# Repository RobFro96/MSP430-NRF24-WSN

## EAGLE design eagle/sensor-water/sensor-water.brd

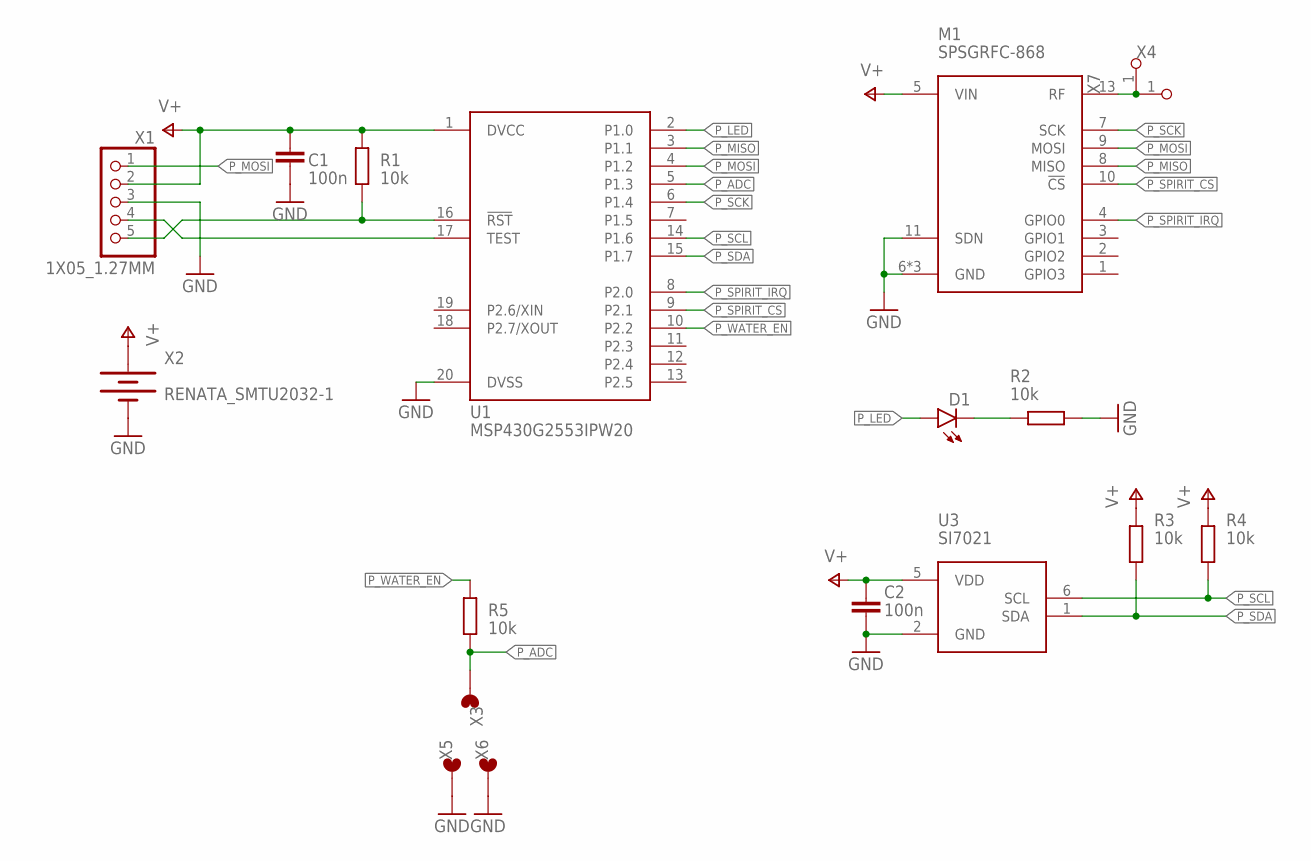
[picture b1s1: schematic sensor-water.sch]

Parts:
C1, C2: 100n; C0805_HAND
D1: LEDCHIPLED_0805; CHIPLED_0805
M1: SPSGRFC-868
R1, R2, R3, R4, R5: 10k; R0805_HAND
U1: MSP430G2553IPW20; PW20
U3: SI7021; DFN6-3X3
X1: 1X05_1.27MM
X2: RENATA_SMTU2032-1
X3, X5, X6: WASSERW_FOOTS
X4, X7: PINHD_1_RND; 1X01_NOSILK

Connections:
GND: C1.2, C2.2, M1.6 (GND), M1.11 (SDN), M1.12 (GND), M1.14 (GND), R2.2, U1.20 (DVSS), U3.2 (GND), X1.3, X2.2 (-), X5.1, X6.1
unnamed: D1.C, R2.1
unnamed: R1.1, U1.16 (!RST!), X1.5
unnamed: U1.17 (TEST), X1.4
unnamed: M1.13 (RF), X4.1, X7.1
P_ADC: R5.1, U1.5 (P1.3), X3.1
P_LED: D1.A, U1.2 (P1.0)
P_MISO: M1.8 (MISO), U1.3 (P1.1)
P_MOSI: M1.9 (MOSI), U1.4 (P1.2), X1.1
P_SCK: M1.7 (SCK), U1.6 (P1.4)
P_SCL: R4.1, U1.14 (P1.6), U3.6 (SCL)
P_SDA: R3.1, U1.15 (P1.7), U3.1 (SDA)
P_SPIRIT_!CS: M1.10 (!CS), U1.9 (P2.1)
P_SPIRIT_IRQ: M1.4 (GPIO0), U1.8 (P2.0)
P_WATER_EN: R5.2, U1.10 (P2.2)
V+: C1.1, C2.1, M1.5 (VIN), R1.2, R3.2, R4.2, U1.1 (DVCC), U3.5 (VDD), X1.2, X2.1 (+)

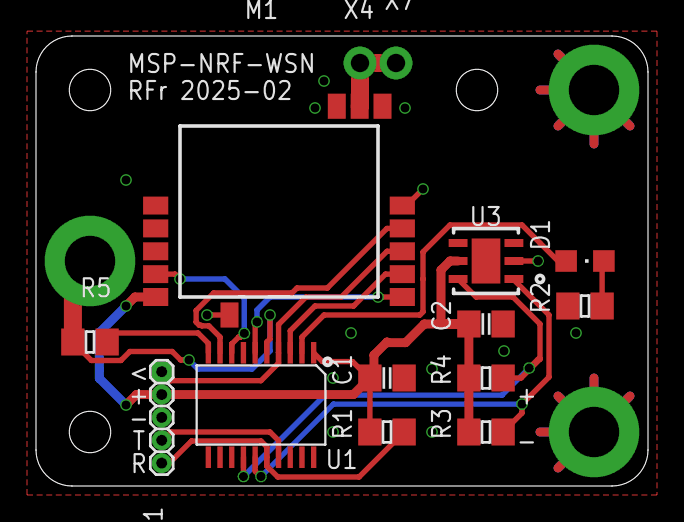
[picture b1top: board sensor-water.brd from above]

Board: 2 copper layers, 34.0 x 25.0 mm, 18 parts (1 on the bottom side), 16 nets.

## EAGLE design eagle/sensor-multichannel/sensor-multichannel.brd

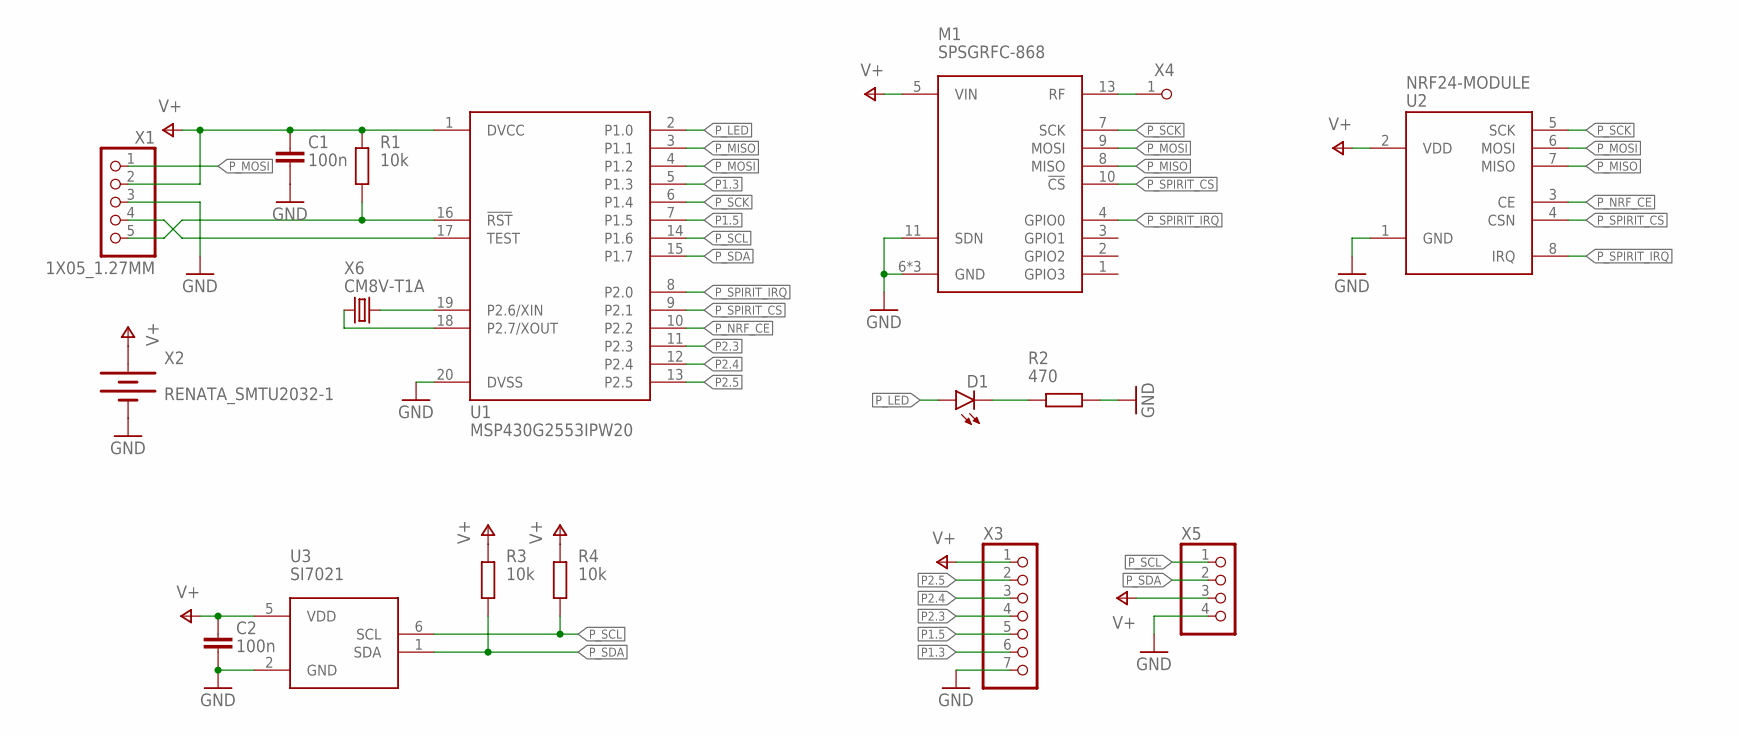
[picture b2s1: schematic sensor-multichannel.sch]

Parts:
C1, C2: 100n; C0603
D1: LEDCHIPLED_0805; CHIPLED_0805
M1: SPSGRFC-868
R1, R3, R4: 10k; R0603
R2: 470; R0603
U1: MSP430G2553IPW20; PW20
U2: NRF24-MODULE
U3: SI7021; DFN6-3X3
X1: 1X05_1.27MM
X2: RENATA_SMTU2032-1
X3: PINHD_7_RNDNS; 1X07_NOSILK
X4: PINHD_1_RND; 1X01_NOSILK
X5: PINHD_4_RNDNS; 1X04_NOSILK
X6: CM8V-T1A

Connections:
GND: C1.2, C2.2, M1.6 (GND), M1.11 (SDN), M1.12 (GND), M1.14 (GND), R2.2, U1.20 (DVSS), U2.1 (GND), U3.2 (GND), X1.3, X2.2 (-), X3.7, X5.4
unnamed: D1.C, R2.1
unnamed: R1.1, U1.16 (!RST!), X1.5
unnamed: U1.17 (TEST), X1.4
unnamed: M1.13 (RF), X4.1
unnamed: U1.19 (P2.6/XIN), X6.P$2 (2)
unnamed: U1.18 (P2.7/XOUT), X6.P$1 (1)
P1.3: U1.5 (P1.3), X3.6
P1.5: U1.7 (P1.5), X3.5
P2.3: U1.11 (P2.3), X3.4
P2.4: U1.12 (P2.4), X3.3
P2.5: U1.13 (P2.5), X3.2
P_LED: D1.A, U1.2 (P1.0)
P_MISO: M1.8 (MISO), U1.3 (P1.1), U2.7 (MISO)
P_MOSI: M1.9 (MOSI), U1.4 (P1.2), U2.6 (MOSI), X1.1
P_NRF_CE: U1.10 (P2.2), U2.3 (CE)
P_SCK: M1.7 (SCK), U1.6 (P1.4), U2.5 (SCK)
P_SCL: R4.1, U1.14 (P1.6), U3.6 (SCL), X5.1
P_SDA: R3.1, U1.15 (P1.7), U3.1 (SDA), X5.2
P_SPIRIT_!CS: M1.10 (!CS), U1.9 (P2.1), U2.4 (CSN)
P_SPIRIT_IRQ: M1.4 (GPIO0), U1.8 (P2.0), U2.8 (IRQ)
V+: C1.1, C2.1, M1.5 (VIN), R1.2, R3.2, R4.2, U1.1 (DVCC), U2.2 (VDD), U3.5 (VDD), X1.2, X2.1 (+), X3.1, X5.3

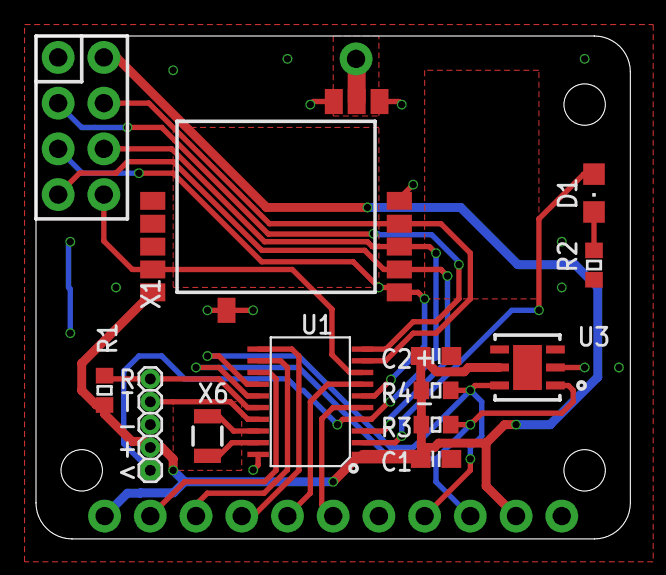
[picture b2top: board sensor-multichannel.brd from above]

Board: 2 copper layers, 33.0 x 27.9 mm, 17 parts (1 on the bottom side), 22 nets.

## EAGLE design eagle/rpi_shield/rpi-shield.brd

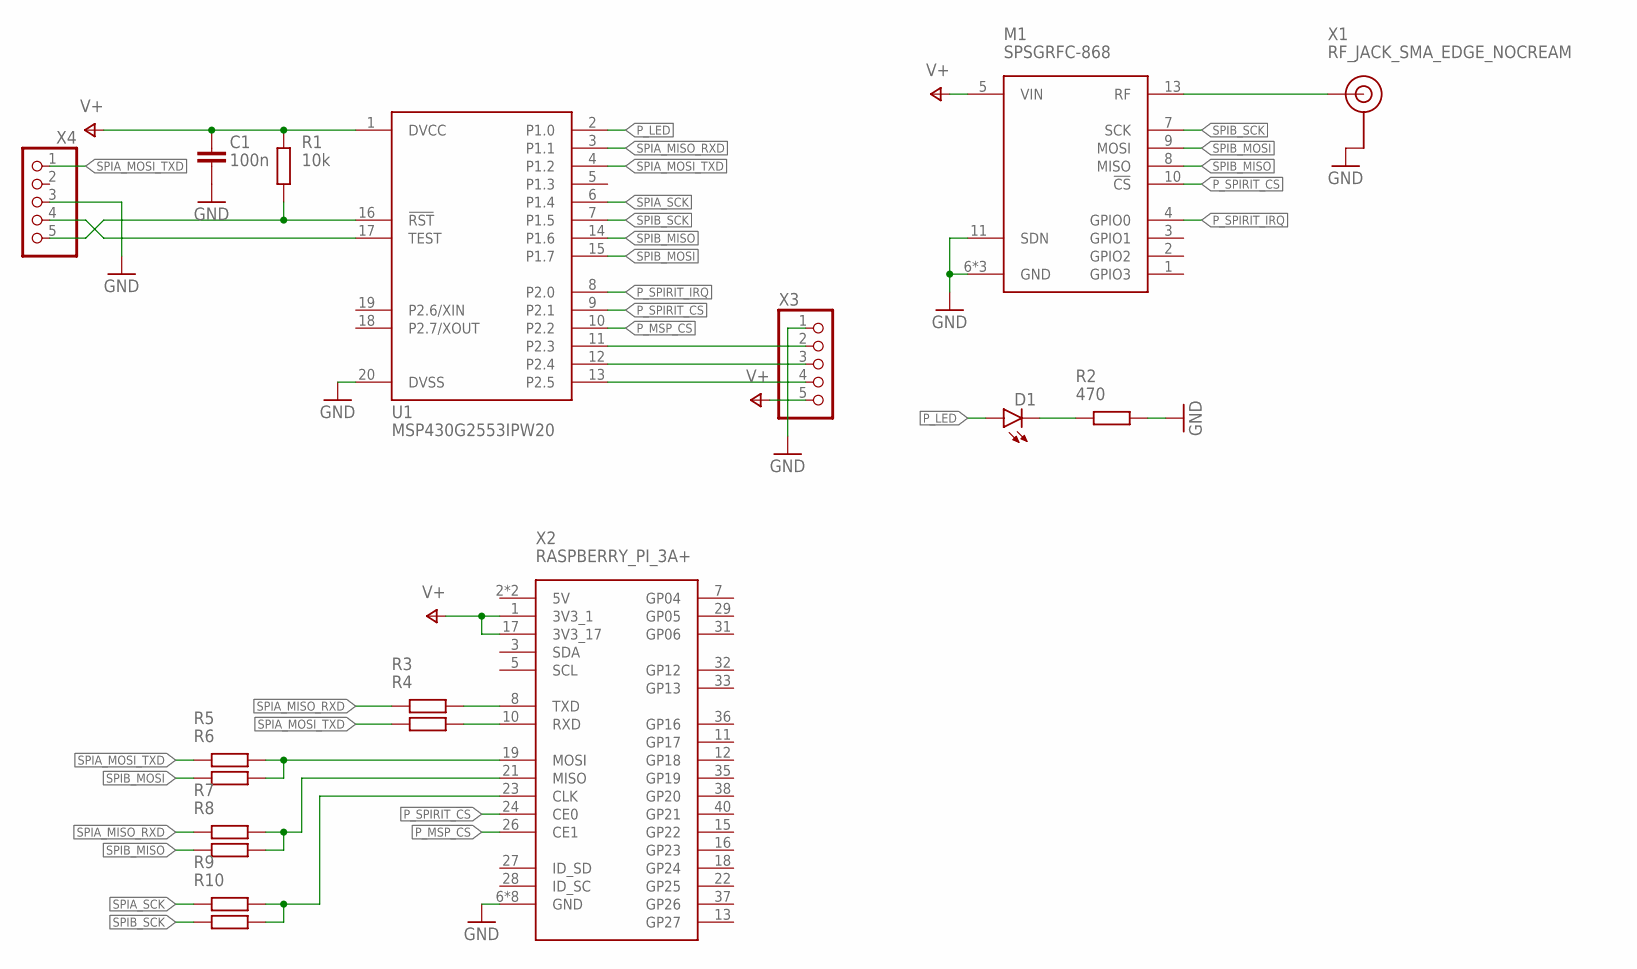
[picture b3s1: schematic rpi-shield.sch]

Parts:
C1: 100n; C0603
D1: LEDCHIPLED_0805; CHIPLED_0805
M1: SPSGRFC-868
R1: 10k; R0603
R2: 470; R0603
R3, R4, R5, R6, R7, R8, R9, R10: R0603_STOP
U1: MSP430G2553IPW20; PW20
X1: RF_JACK_SMA_EDGE_NOCREAM; RF_SMA_JACK_EDGE_NOCREAM
X2: RASPBERRY_PI_3A+
X3, X4: PINHD_5_RND; 1X05

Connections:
GND: C1.2, M1.6 (GND), M1.11 (SDN), M1.12 (GND), M1.14 (GND), R2.2, U1.20 (DVSS), X1.2 (GND), X1.3 (GND), X1.4 (GND), X1.5 (GND), X2.6 (GND), X2.9 (GND), X2.14 (GND), X2.20 (GND), X2.25 (GND), X2.30 (GND), X2.34 (GND), X2.39 (GND), X3.1, X4.3
unnamed: D1.C, R2.1
unnamed: R1.1, U1.16 (!RST!), X4.5
unnamed: U1.17 (TEST), X4.4
unnamed: M1.13 (RF), X1.1 (SIGNAL)
unnamed: R3.2, X2.8 (TXD)
unnamed: R4.2, X2.10 (RXD)
unnamed: R5.2, R6.2, X2.19 (MOSI)
unnamed: R7.2, R8.2, X2.21 (MISO)
unnamed: R9.2, R10.2, X2.23 (CLK)
unnamed: U1.13 (P2.5), X3.4
unnamed: U1.12 (P2.4), X3.3
unnamed: U1.11 (P2.3), X3.2
P_LED: D1.A, U1.2 (P1.0)
P_MSP_!CS: U1.10 (P2.2), X2.26 (CE1)
P_SPIRIT_!CS: M1.10 (!CS), U1.9 (P2.1), X2.24 (CE0)
P_SPIRIT_IRQ: M1.4 (GPIO0), U1.8 (P2.0)
SPIA_MISO_RXD: R3.1, R7.1, U1.3 (P1.1)
SPIA_MOSI_TXD: R4.1, R5.1, U1.4 (P1.2), X4.1
SPIA_SCK: R9.1, U1.6 (P1.4)
SPIB_MISO: M1.8 (MISO), R8.1, U1.14 (P1.6)
SPIB_MOSI: M1.9 (MOSI), R6.1, U1.15 (P1.7)
SPIB_SCK: M1.7 (SCK), R10.1, U1.7 (P1.5)
V+: C1.1, M1.5 (VIN), R1.2, U1.1 (DVCC), X2.1 (3V3_1), X2.17 (3V3_17), X3.5

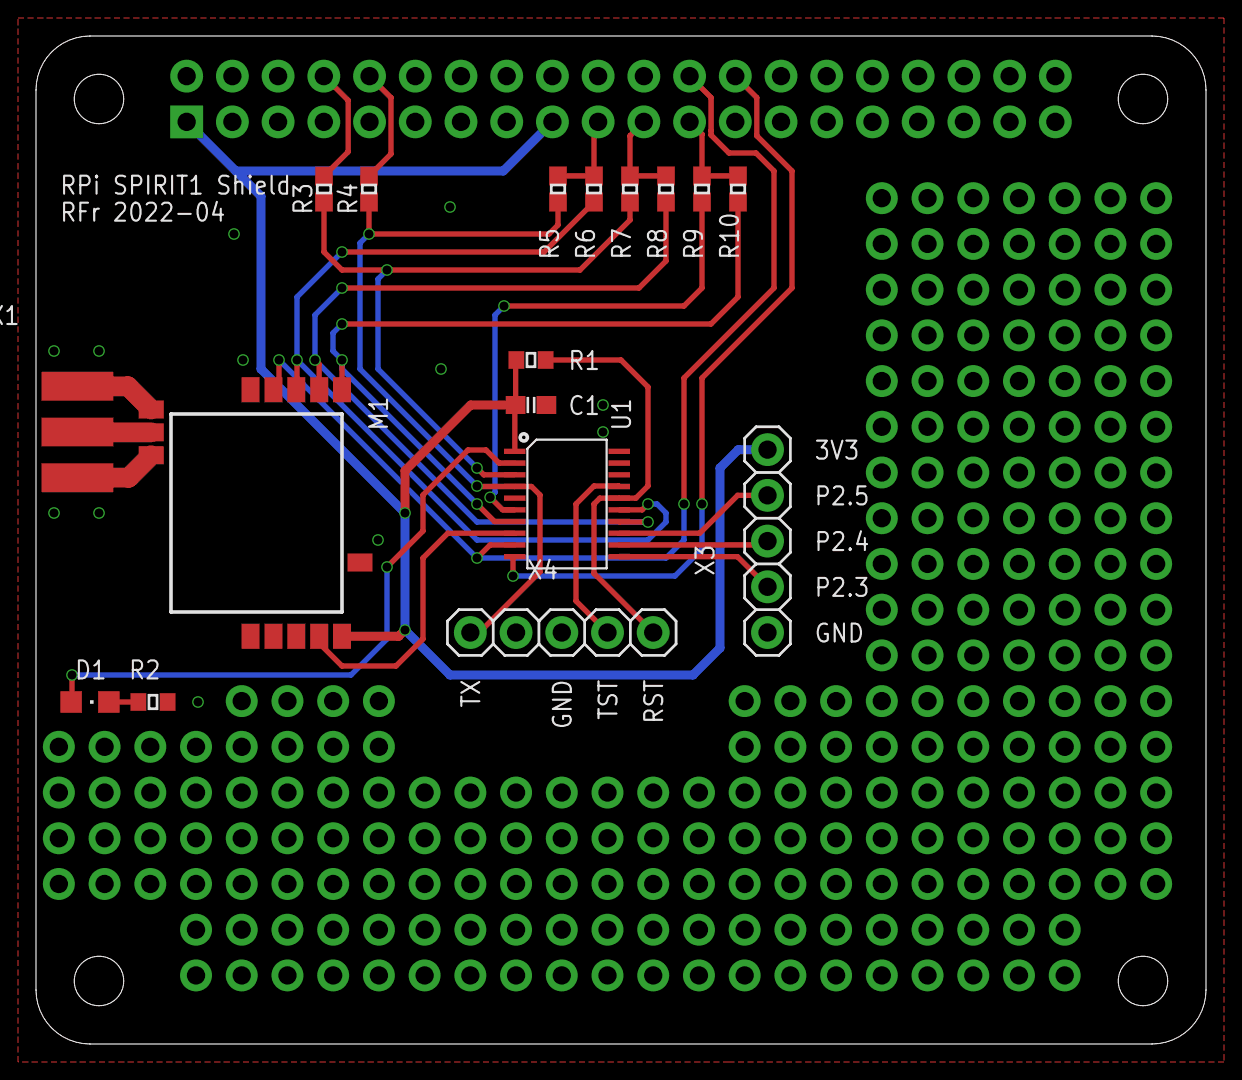
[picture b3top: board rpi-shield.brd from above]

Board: 2 copper layers, 65.0 x 56.0 mm, 18 parts (0 on the bottom side), 24 nets.

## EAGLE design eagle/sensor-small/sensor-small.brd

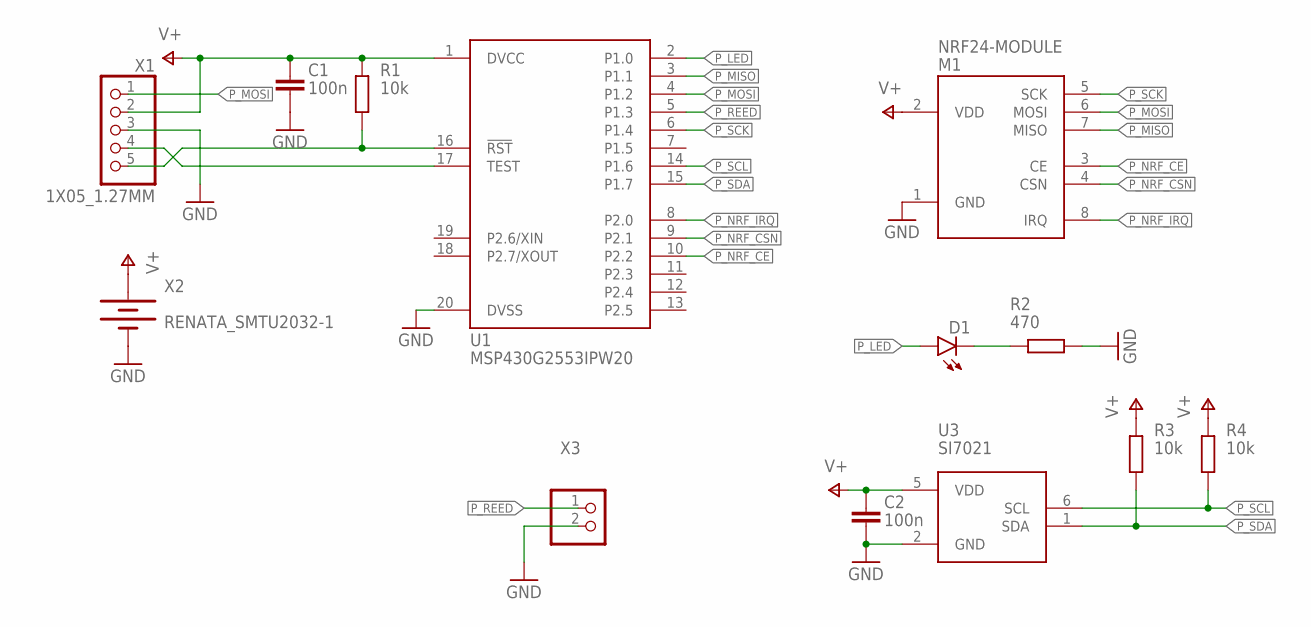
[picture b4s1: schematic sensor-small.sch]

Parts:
C1, C2: 100n; C0603
D1: LEDCHIPLED_0805; CHIPLED_0805
M1: NRF24-MODULE
R1, R3, R4: 10k; R0603
R2: 470; R0603
U1: MSP430G2553IPW20; PW20
U3: SI7021; DFN6-3X3
X1: 1X05_1.27MM
X2: RENATA_SMTU2032-1
X3: PINHD_2_RND; 1X02

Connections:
GND: C1.2, C2.2, M1.1 (GND), R2.2, U1.20 (DVSS), U3.2 (GND), X1.3, X2.2 (-), X3.2
unnamed: D1.C, R2.1
unnamed: R1.1, U1.16 (!RST!), X1.5
unnamed: U1.17 (TEST), X1.4
P_LED: D1.A, U1.2 (P1.0)
P_MISO: M1.7 (MISO), U1.3 (P1.1)
P_MOSI: M1.6 (MOSI), U1.4 (P1.2), X1.1
P_NRF_CE: M1.3 (CE), U1.10 (P2.2)
P_NRF_CSN: M1.4 (CSN), U1.9 (P2.1)
P_NRF_IRQ: M1.8 (IRQ), U1.8 (P2.0)
P_REED: U1.5 (P1.3), X3.1
P_SCK: M1.5 (SCK), U1.6 (P1.4)
P_SCL: R4.1, U1.14 (P1.6), U3.6 (SCL)
P_SDA: R3.1, U1.15 (P1.7), U3.1 (SDA)
V+: C1.1, C2.1, M1.2 (VDD), R1.2, R3.2, R4.2, U1.1 (DVCC), U3.5 (VDD), X1.2, X2.1 (+)

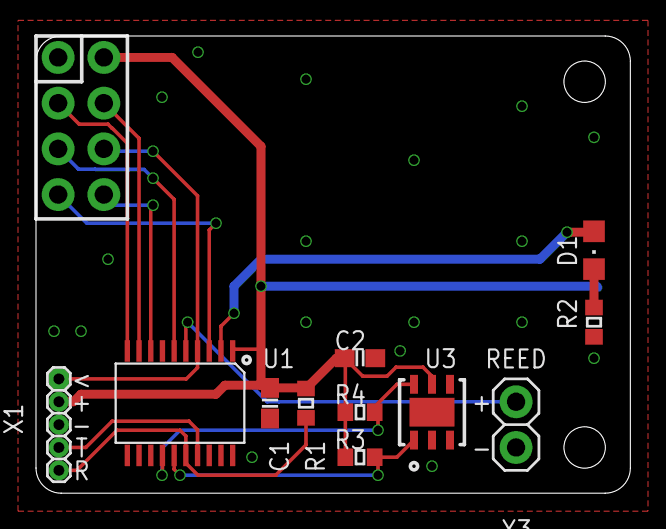
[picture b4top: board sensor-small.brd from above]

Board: 2 copper layers, 33.0 x 25.4 mm, 13 parts (1 on the bottom side), 15 nets.

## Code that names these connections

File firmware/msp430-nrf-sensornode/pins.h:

/**
 * MSP430 and NRF24L01 based WSN
 * @file pins.h
 * @author Robert Fromm
 * @date 06.02.2022
 *
 * This file is generated by the MSP430 Pinmapper.
 * Copy the following JSON code into Pinmapper program to edit project.
 * {"definitions":[{"name":"LED","pin":"P1.0","functions":[{"dir":"1","out":"0","sel":"-","sel2":"-","in":"-","ren":"-","ie":"-","ies":"-","ifg":"-","name":"setup","type":"set"},{"dir":"-","out":"1","sel":"-","sel2":"-","in":"-","ren":"-","ie":"-","ies":"-","ifg":"-","name":"h","type":"set"},{"dir":"-","out":"0","sel":"-","sel2":"-","in":"-","ren":"-","ie":"-","ies":"-","ifg":"-","name":"l","type":"set"}]},{"name":"SPIA_MISO","pin":"P1.1","functions":[{"dir":"-","out":"0","sel":"1","sel2":"1","in":"-","ren":"1","ie":"-","ies":"-","ifg":"-","name":"setup","type":"set"}]},{"name":"SPIA_MOSI","pin":"P1.2","functions":[{"dir":"-","out":"-","sel":"1","sel2":"1","in":"-","ren":"-","ie":"-","ies":"-","ifg":"-","name":"setup","type":"set"}]},{"name":"REED","pin":"P1.3","functions":[{"dir":"0","out":"0","sel":"-","sel2":"-","in":"-","ren":"1","ie":"-","ies":"-","ifg":"-","name":"setup","type":"set"},{"dir":"-","out":"-","sel":"-","sel2":"-","in":"?","ren":"-","ie":"-","ies":"-","ifg":"-","name":"val","type":"get"},{"dir":"-","out":"1","sel":"-","sel2":"-","in":"-","ren":"1","ie":"-","ies":"-","ifg":"-","name":"pullup","type":"set"},{"dir":"-","out":"0","sel":"-","sel2":"-","in":"-","ren":"1","ie":"-","ies":"-","ifg":"-","name":"pulldown","type":"set"}]},{"name":"SPIA_SCK","pin":"P1.4","functions":[{"dir":"-","out":"-","sel":"1","sel2":"1","in":"-","ren":"-","ie":"-","ies":"-","ifg":"-","name":"setup","type":"set"},{"dir":"1","out":"0","sel":"0","sel2":"0","in":"-","ren":"-","ie":"-","ies":"-","ifg":"-","name":"mode_gpio","type":"set"},{"dir":"-","out":"1","sel":"-","sel2":"-","in":"-","ren":"-","ie":"-","ies":"-","ifg":"-","name":"h","type":"set"},{"dir":"-","out":"0","sel":"-","sel2":"-","in":"-","ren":"-","ie":"-","ies":"-","ifg":"-","name":"l","type":"set"}]},{"name":"NRF_IRQ","pin":"P2.0","functions":[{"dir":"0","out":"1","sel":"-","sel2":"-","in":"-","ren":"1","ie":"1","ies":"1","ifg":"0","name":"setup","type":"set"},{"dir":"-","out":"-","sel":"-","sel2":"-","in":"?","ren":"-","ie":"-","ies":"-","ifg":"-","name":"val","type":"get"},{"dir":"-","out":"-","sel":"-","sel2":"-","in":"-","ren":"-","ie":"-","ies":"-","ifg":"?","name":"ifg","type":"get"},{"dir":"-","out":"-","sel":"-","sel2":"-","in":"-","ren":"-","ie":"-","ies":"-","ifg":"0","name":"ifg_clr","type":"set"}]},{"name":"NRF_CS","pin":"P2.1","functions":[{"dir":"1","out":"1","sel":"-","sel2":"-","in":"-","ren":"-","ie":"-","ies":"-","ifg":"-","name":"setup","type":"set"},{"dir":"-","out":"1","sel":"-","sel2":"-","in":"-","ren":"-","ie":"-","ies":"-","ifg":"-","name":"h","type":"set"},{"dir":"-","out":"0","sel":"-","sel2":"-","in":"-","ren":"-","ie":"-","ies":"-","ifg":"-","name":"l","type":"set"}]},{"name":"NRF_CE","pin":"P2.2","functions":[{"dir":"1","out":"1","sel":"-","sel2":"-","in":"-","ren":"-","ie":"-","ies":"-","ifg":"-","name":"setup","type":"set"},{"dir":"-","out":"1","sel":"-","sel2":"-","in":"-","ren":"-","ie":"-","ies":"-","ifg":"-","name":"h","type":"set"},{"dir":"-","out":"0","sel":"-","sel2":"-","in":"-","ren":"-","ie":"-","ies":"-","ifg":"-","name":"l","type":"set"}]},{"name":"I2C_SDA","pin":"P1.7","functions":[{"dir":"-","out":"-","sel":"1","sel2":"1","in":"-","ren":"-","ie":"-","ies":"-","ifg":"-","name":"setup","type":"set"}]},{"name":"I2C_SCL","pin":"P1.6","functions":[{"dir":"-","out":"-","sel":"1","sel2":"1","in":"-","ren":"-","ie":"-","ies":"-","ifg":"-","name":"setup","type":"set"}]}],"device":"MSP430G2553","xinXout":true,"filename":"pins.h","prefix":"p_","dcoCalibration":true,"delayFunctions":true,"doxygenHeader":"MSP430 and NRF24L01 based WSN\n@file pins.h\n@author Robert Fromm\n@date 06.02.2022\n\nThis file is generated by the MSP430 Pinmapper.\nCopy the following JSON code into Pinmapper program to edit project."}
 */

#ifndef PINS_H_
#define PINS_H_

#include <msp430.h>
#if defined P_CLOCK_FREQ_1_MHZ
#define P_CLOCK_FREQ_MHZ 1
#elif defined P_CLOCK_FREQ_8_MHZ
#define P_CLOCK_FREQ_MHZ 8
#elif defined P_CLOCK_FREQ_12_MHZ
#define P_CLOCK_FREQ_MHZ 12
#elif defined P_CLOCK_FREQ_16_MHZ
#define P_CLOCK_FREQ_MHZ 16
#else
#include "config.h"
#endif

// PORT 1
#define P_LED BIT0
#define P_SPIA_MISO BIT1
#define P_SPIA_MOSI BIT2
#define P_REED BIT3
#define P_SPIA_SCK BIT4
#define P_I2C_SCL BIT6
#define P_I2C_SDA BIT7
#define P_PORT1_UNUSED (BIT5)

// PORT 2
#define P_NRF_IRQ BIT0
#define P_NRF_CS BIT1
#define P_NRF_CE BIT2
#define P_XIN BIT6
#define P_XOUT BIT7
#define P_PORT2_UNUSED (BIT3 + BIT4 + BIT5)

// PORT 3
#define P_PORT3_UNUSED (BIT0 + BIT1 + BIT2 + BIT3 + BIT4 + BIT5 + BIT6 + BIT7)

// LED @ P1.0
#define p_led_setup() ({P1OUT &=~ P_LED; P1DIR |= P_LED;})
#define p_led_h() ({P1OUT |= P_LED;})
#define p_led_l() ({P1OUT &=~ P_LED;})

// SPIA_MISO @ P1.1
#define p_spia_miso_setup() ({P1SEL |= P_SPIA_MISO; P1SEL2 |= P_SPIA_MISO; P1OUT &=~ P_SPIA_MISO; P1REN |= P_SPIA_MISO;})

// SPIA_MOSI @ P1.2
#define p_spia_mosi_setup() ({P1SEL |= P_SPIA_MOSI; P1SEL2 |= P_SPIA_MOSI;})

// REED @ P1.3
#define p_reed_setup() ({P1OUT &=~ P_REED; P1DIR &=~ P_REED; P1REN |= P_REED;})
#define p_reed_val() ({P1IN & P_REED;})
#define p_reed_pullup() ({P1OUT |= P_REED; P1REN |= P_REED;})
#define p_reed_pulldown() ({P1OUT &=~ P_REED; P1REN |= P_REED;})

// SPIA_SCK @ P1.4
#define p_spia_sck_setup() ({P1SEL |= P_SPIA_SCK; P1SEL2 |= P_SPIA_SCK;})
#define p_spia_sck_mode_gpio() ({P1SEL &=~ P_SPIA_SCK; P1SEL2 &=~ P_SPIA_SCK; P1OUT &=~ P_SPIA_SCK; P1DIR |= P_SPIA_SCK;})
#define p_spia_sck_h() ({P1OUT |= P_SPIA_SCK;})
#define p_spia_sck_l() ({P1OUT &=~ P_SPIA_SCK;})

// NRF_IRQ @ P2.0
#define p_nrf_irq_setup() ({P2OUT |= P_NRF_IRQ; P2DIR &=~ P_NRF_IRQ; P2REN |= P_NRF_IRQ; P2IES |= P_NRF_IRQ; P2IFG &=~ P_NRF_IRQ; P2IE |= P_NRF_IRQ;})
#define p_nrf_irq_val() ({P2IN & P_NRF_IRQ;})
#define p_nrf_irq_ifg() ({P2IFG & P_NRF_IRQ;})
#define p_nrf_irq_ifg_clr() ({P2IFG &=~ P_NRF_IRQ;})

// NRF_CS @ P2.1
#define p_nrf_cs_setup() ({P2OUT |= P_NRF_CS; P2DIR |= P_NRF_CS;})
#define p_nrf_cs_h() ({P2OUT |= P_NRF_CS;})
#define p_nrf_cs_l() ({P2OUT &=~ P_NRF_CS;})

// NRF_CE @ P2.2
#define p_nrf_ce_setup() ({P2OUT |= P_NRF_CE; P2DIR |= P_NRF_CE;})
#define p_nrf_ce_h() ({P2OUT |= P_NRF_CE;})
#define p_nrf_ce_l() ({P2OUT &=~ P_NRF_CE;})

// I2C_SDA @ P1.7
#define p_i2c_sda_setup() ({P1SEL |= P_I2C_SDA; P1SEL2 |= P_I2C_SDA;})

// I2C_SCL @ P1.6
#define p_i2c_scl_setup() ({P1SEL |= P_I2C_SCL; P1SEL2 |= P_I2C_SCL;})

// SETUP
inline void p_setup() {
    //Clock Calibration
#if P_CLOCK_FREQ_MHZ == 1
    BCSCTL1 = CALBC1_1MHZ;
    DCOCTL = CALDCO_1MHZ;
#elif P_CLOCK_FREQ_MHZ == 8
    BCSCTL1 = CALBC1_8MHZ;
    DCOCTL = CALDCO_8MHZ;
#elif P_CLOCK_FREQ_MHZ == 12
    BCSCTL1 = CALBC1_12MHZ;
    DCOCTL = CALDCO_12MHZ;
#elif P_CLOCK_FREQ_MHZ == 16
    BCSCTL1 = CALBC1_16MHZ;
    DCOCTL = CALDCO_16MHZ;
#endif

    // Pin Setup
    p_led_setup();
    p_spia_miso_setup();
    p_spia_mosi_setup();
    p_reed_setup();
    p_spia_sck_setup();
    p_nrf_irq_setup();
    p_nrf_cs_setup();
    p_nrf_ce_setup();
    p_i2c_sda_setup();
    p_i2c_scl_setup();

    // Unused Pins
    P1OUT &= ~ P_PORT1_UNUSED;
    P1REN |= P_PORT1_UNUSED;
    P2OUT &= ~ P_PORT2_UNUSED;
    P2REN |= P_PORT2_UNUSED;
    P3OUT &= ~ P_PORT3_UNUSED;
    P3REN |= P_PORT3_UNUSED;
}

#define p_delay_ms(t) (__delay_cycles(P_CLOCK_FREQ_MHZ * 1000L * (t)))
#define p_delay_us(t) (__delay_cycles(P_CLOCK_FREQ_MHZ * (t)))

#endif

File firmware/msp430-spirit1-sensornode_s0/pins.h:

/**
 * THE WAKEUP RECEIVER PROJECT
 * @file pins.h
 * @author Robert Fromm
 * @date 08.12.2020
 *
 * This file is generated by the MSP430 Pinmapper.
 * Copy the following JSON code into Pinmapper program to edit project.
 * {"definitions":[{"name":"LED","pin":"P1.0","functions":[{"dir":"1","out":"0","sel":"-","sel2":"-","in":"-","ren":"-","ie":"-","ies":"-","ifg":"-","name":"setup","type":"set"},{"dir":"-","out":"1","sel":"-","sel2":"-","in":"-","ren":"-","ie":"-","ies":"-","ifg":"-","name":"h","type":"set"},{"dir":"-","out":"0","sel":"-","sel2":"-","in":"-","ren":"-","ie":"-","ies":"-","ifg":"-","name":"l","type":"set"}]},{"name":"SPIA_MISO","pin":"P1.1","functions":[{"dir":"-","out":"0","sel":"1","sel2":"1","in":"-","ren":"1","ie":"-","ies":"-","ifg":"-","name":"setup","type":"set"}]},{"name":"SPIA_MOSI","pin":"P1.2","functions":[{"dir":"-","out":"-","sel":"1","sel2":"1","in":"-","ren":"-","ie":"-","ies":"-","ifg":"-","name":"setup","type":"set"}]},{"name":"SPIA_SCK","pin":"P1.4","functions":[{"dir":"-","out":"-","sel":"1","sel2":"1","in":"-","ren":"-","ie":"-","ies":"-","ifg":"-","name":"setup","type":"set"},{"dir":"1","out":"0","sel":"0","sel2":"0","in":"-","ren":"-","ie":"-","ies":"-","ifg":"-","name":"mode_gpio","type":"set"},{"dir":"-","out":"1","sel":"-","sel2":"-","in":"-","ren":"-","ie":"-","ies":"-","ifg":"-","name":"h","type":"set"},{"dir":"-","out":"0","sel":"-","sel2":"-","in":"-","ren":"-","ie":"-","ies":"-","ifg":"-","name":"l","type":"set"}]},{"name":"SPIRIT_IRQ","pin":"P2.0","functions":[{"dir":"0","out":"1","sel":"-","sel2":"-","in":"-","ren":"1","ie":"1","ies":"1","ifg":"0","name":"setup","type":"set"},{"dir":"-","out":"-","sel":"-","sel2":"-","in":"?","ren":"-","ie":"-","ies":"-","ifg":"-","name":"val","type":"get"},{"dir":"-","out":"-","sel":"-","sel2":"-","in":"-","ren":"-","ie":"-","ies":"-","ifg":"?","name":"ifg","type":"get"},{"dir":"-","out":"-","sel":"-","sel2":"-","in":"-","ren":"-","ie":"-","ies":"-","ifg":"0","name":"ifg_clr","type":"set"}]},{"name":"SPIRIT_CS","pin":"P2.1","functions":[{"dir":"1","out":"1","sel":"-","sel2":"-","in":"-","ren":"-","ie":"-","ies":"-","ifg":"-","name":"setup","type":"set"},{"dir":"-","out":"1","sel":"-","sel2":"-","in":"-","ren":"-","ie":"-","ies":"-","ifg":"-","name":"h","type":"set"},{"dir":"-","out":"0","sel":"-","sel2":"-","in":"-","ren":"-","ie":"-","ies":"-","ifg":"-","name":"l","type":"set"}]},{"name":"S0","pin":"P1.3","functions":[{"dir":"0","out":"1","sel":"-","sel2":"-","in":"-","ren":"1","ie":"1","ies":"1","ifg":"0","name":"setup","type":"set"},{"dir":"-","out":"-","sel":"-","sel2":"-","in":"?","ren":"-","ie":"-","ies":"-","ifg":"-","name":"val","type":"get"},{"dir":"-","out":"-","sel":"-","sel2":"-","in":"-","ren":"-","ie":"-","ies":"-","ifg":"?","name":"ifg","type":"get"},{"dir":"-","out":"-","sel":"-","sel2":"-","in":"-","ren":"-","ie":"-","ies":"-","ifg":"0","name":"ifg_clr","type":"set"}]}],"device":"MSP430G2553","xinXout":true,"filename":"pins.h","prefix":"p_","dcoCalibration":true,"delayFunctions":true,"doxygenHeader":"THE WAKEUP RECEIVER PROJECT\n@file pins.h\n@author Robert Fromm\n@date 08.12.2020\n\nThis file is generated by the MSP430 Pinmapper.\nCopy the following JSON code into Pinmapper program to edit project."}
 */

#ifndef PINS_H_
#define PINS_H_

#include <msp430.h>
#if defined P_CLOCK_FREQ_1_MHZ
#define P_CLOCK_FREQ_MHZ 1
#elif defined P_CLOCK_FREQ_8_MHZ
#define P_CLOCK_FREQ_MHZ 8
#elif defined P_CLOCK_FREQ_12_MHZ
#define P_CLOCK_FREQ_MHZ 12
#elif defined P_CLOCK_FREQ_16_MHZ
#define P_CLOCK_FREQ_MHZ 16
#else
#include "config.h"
#endif

// PORT 1
#define P_LED BIT0
#define P_SPIA_MISO BIT1
#define P_SPIA_MOSI BIT2
#define P_S0 BIT3
#define P_SPIA_SCK BIT4
#define P_PORT1_UNUSED (BIT5 + BIT6 + BIT7)

// PORT 2
#define P_SPIRIT_IRQ BIT0
#define P_SPIRIT_CS BIT1
#define P_XIN BIT6
#define P_XOUT BIT7
#define P_PORT2_UNUSED (BIT2 + BIT3 + BIT4 + BIT5)

// PORT 3
#define P_PORT3_UNUSED (BIT0 + BIT1 + BIT2 + BIT3 + BIT4 + BIT5 + BIT6 + BIT7)

// LED @ P1.0
#define p_led_setup() ({P1OUT &=~ P_LED; P1DIR |= P_LED;})
#define p_led_h() ({P1OUT |= P_LED;})
#define p_led_l() ({P1OUT &=~ P_LED;})

// SPIA_MISO @ P1.1
#define p_spia_miso_setup() ({P1SEL |= P_SPIA_MISO; P1SEL2 |= P_SPIA_MISO; P1OUT &=~ P_SPIA_MISO; P1REN |= P_SPIA_MISO;})

// SPIA_MOSI @ P1.2
#define p_spia_mosi_setup() ({P1SEL |= P_SPIA_MOSI; P1SEL2 |= P_SPIA_MOSI;})

// SPIA_SCK @ P1.4
#define p_spia_sck_setup() ({P1SEL |= P_SPIA_SCK; P1SEL2 |= P_SPIA_SCK;})
#define p_spia_sck_mode_gpio() ({P1SEL &=~ P_SPIA_SCK; P1SEL2 &=~ P_SPIA_SCK; P1OUT &=~ P_SPIA_SCK; P1DIR |= P_SPIA_SCK;})
#define p_spia_sck_h() ({P1OUT |= P_SPIA_SCK;})
#define p_spia_sck_l() ({P1OUT &=~ P_SPIA_SCK;})

// SPIRIT_IRQ @ P2.0
#define p_spirit_irq_setup() ({P2OUT |= P_SPIRIT_IRQ; P2DIR &=~ P_SPIRIT_IRQ; P2REN |= P_SPIRIT_IRQ; P2IES |= P_SPIRIT_IRQ; P2IFG &=~ P_SPIRIT_IRQ; P2IE |= P_SPIRIT_IRQ;})
#define p_spirit_irq_val() ({P2IN & P_SPIRIT_IRQ;})
#define p_spirit_irq_ifg() ({P2IFG & P_SPIRIT_IRQ;})
#define p_spirit_irq_ifg_clr() ({P2IFG &=~ P_SPIRIT_IRQ;})

// SPIRIT_CS @ P2.1
#define p_spirit_cs_setup() ({P2OUT |= P_SPIRIT_CS; P2DIR |= P_SPIRIT_CS;})
#define p_spirit_cs_h() ({P2OUT |= P_SPIRIT_CS;})
#define p_spirit_cs_l() ({P2OUT &=~ P_SPIRIT_CS;})

// S0 @ P1.3
#define p_s0_setup() ({P1OUT |= P_S0; P1DIR &=~ P_S0; P1REN |= P_S0; P1IES |= P_S0; P1IFG &=~ P_S0; P1IE |= P_S0;})
#define p_s0_val() ({P1IN & P_S0;})
#define p_s0_ifg() ({P1IFG & P_S0;})
#define p_s0_ifg_clr() ({P1IFG &=~ P_S0;})

// SETUP
inline void p_setup() {
    //Clock Calibration
#if P_CLOCK_FREQ_MHZ == 1
    BCSCTL1 = CALBC1_1MHZ;
    DCOCTL = CALDCO_1MHZ;
#elif P_CLOCK_FREQ_MHZ == 8
    BCSCTL1 = CALBC1_8MHZ;
    DCOCTL = CALDCO_8MHZ;
#elif P_CLOCK_FREQ_MHZ == 12
    BCSCTL1 = CALBC1_12MHZ;
    DCOCTL = CALDCO_12MHZ;
#elif P_CLOCK_FREQ_MHZ == 16
    BCSCTL1 = CALBC1_16MHZ;
    DCOCTL = CALDCO_16MHZ;
#endif

    // Pin Setup
    p_led_setup();
    p_spia_miso_setup();
    p_spia_mosi_setup();
    p_spia_sck_setup();
    p_spirit_irq_setup();
    p_spirit_cs_setup();
    p_s0_setup();

    // Unused Pins
    P1OUT &= ~ P_PORT1_UNUSED;
    P1REN |= P_PORT1_UNUSED;
    P2OUT &= ~ P_PORT2_UNUSED;
    P2REN |= P_PORT2_UNUSED;
    P3OUT &= ~ P_PORT3_UNUSED;
    P3REN |= P_PORT3_UNUSED;
}

#define p_delay_ms(t) (__delay_cycles(P_CLOCK_FREQ_MHZ * 1000L * (t)))
#define p_delay_us(t) (__delay_cycles(P_CLOCK_FREQ_MHZ * (t)))

#endif

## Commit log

2022-02-10 MSP430 implementation for NRF24L01 physical layer
2022-02-10 Added datasheets
2022-02-11 Added gitignore
2022-02-11 Renamed firmware Code Composer Studio project
2022-02-11 Added internal temperature measurement and Si7021 support
2022-02-12 Updated gitignore
2022-02-12 Moved data collection to own module
2022-02-12 Added support form BMP180 temperature and pressure sensor
2022-02-12 Added support for a reed switch
2022-02-13 Added eagle/ directory, central design on Perfboard
2022-02-13 Added central Code Composer project, NRF24 addressing, communication test
2022-02-13 Added sensor to central communication and retry logic
2022-02-14 Added in_regs and acknowledgement
2022-02-15 started central housing 3D design
2022-02-17 out_regs.retries not to reset until successful transmission
2022-02-17 Added support for VLO clock and added function isr_delay_ms() embedded mulitplication with clock frequency estimate
2022-02-17 Added Eagle schematic and layout for small sensor board
2022-02-18 Fixed swapped RST and TEST line in EAGLE design
2022-02-19 Finished 3D design of central housing (performing test print)
2022-02-19 Finished sensor programming, added measurements for battery life time estimations
2022-02-20 Added Eagle design for weather station on perfboard, changed config.h accordingly
2022-02-20 Added 3D design for weather station PCB holder
2022-02-20 Finished Central firmware to send out_regs and receiver in_regs over UART
2022-02-20 Added RF channel to MSP430 firmware configuration
2022-02-24 Added server, write incoming data to database
2022-02-24 Added server sending in_regs to central
2022-02-26 Added conditional LED output
2022-03-06 Changed LED resistor value
2022-03-06 Started server frontend
2022-03-06 Added sensor housing 3D design
2022-03-27 Added sensor housing design, without magnetic holder
2022-04-03 Changes in Config
2022-04-03 Added Server Frontend and Graph Generator
2022-04-09 Added EAGLE design for Sensor and Raspberry Pi Shield for SPIRIT1 868 MHz transceiver
2022-05-21 Added SPIRIT1 based firmware - test program
2022-05-22 Added old sensornode functionality to SPIRIT1 project
2022-05-22 Added old functionality to central, RPi runnig successfully
2022-07-16 Added receiver RSSI value to out_regs and database
2025-01-05 Big change: Simplified firmware to use lists instead of registers, adapted central firmware, too
2025-01-08 Added Sensor with S0 interface for energy meter
2025-02-25 Added EAGLE designs
2025-02-25 Firmware cleanup
